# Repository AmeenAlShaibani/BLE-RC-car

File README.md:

The goal of this project is to create an Android app accompanied by a motherboard for an RC car. The motherboard will handle signal, and power distribution to the motors,
and will use BLE technology to connect to the Android app such that the RC car can be controlled remotely.

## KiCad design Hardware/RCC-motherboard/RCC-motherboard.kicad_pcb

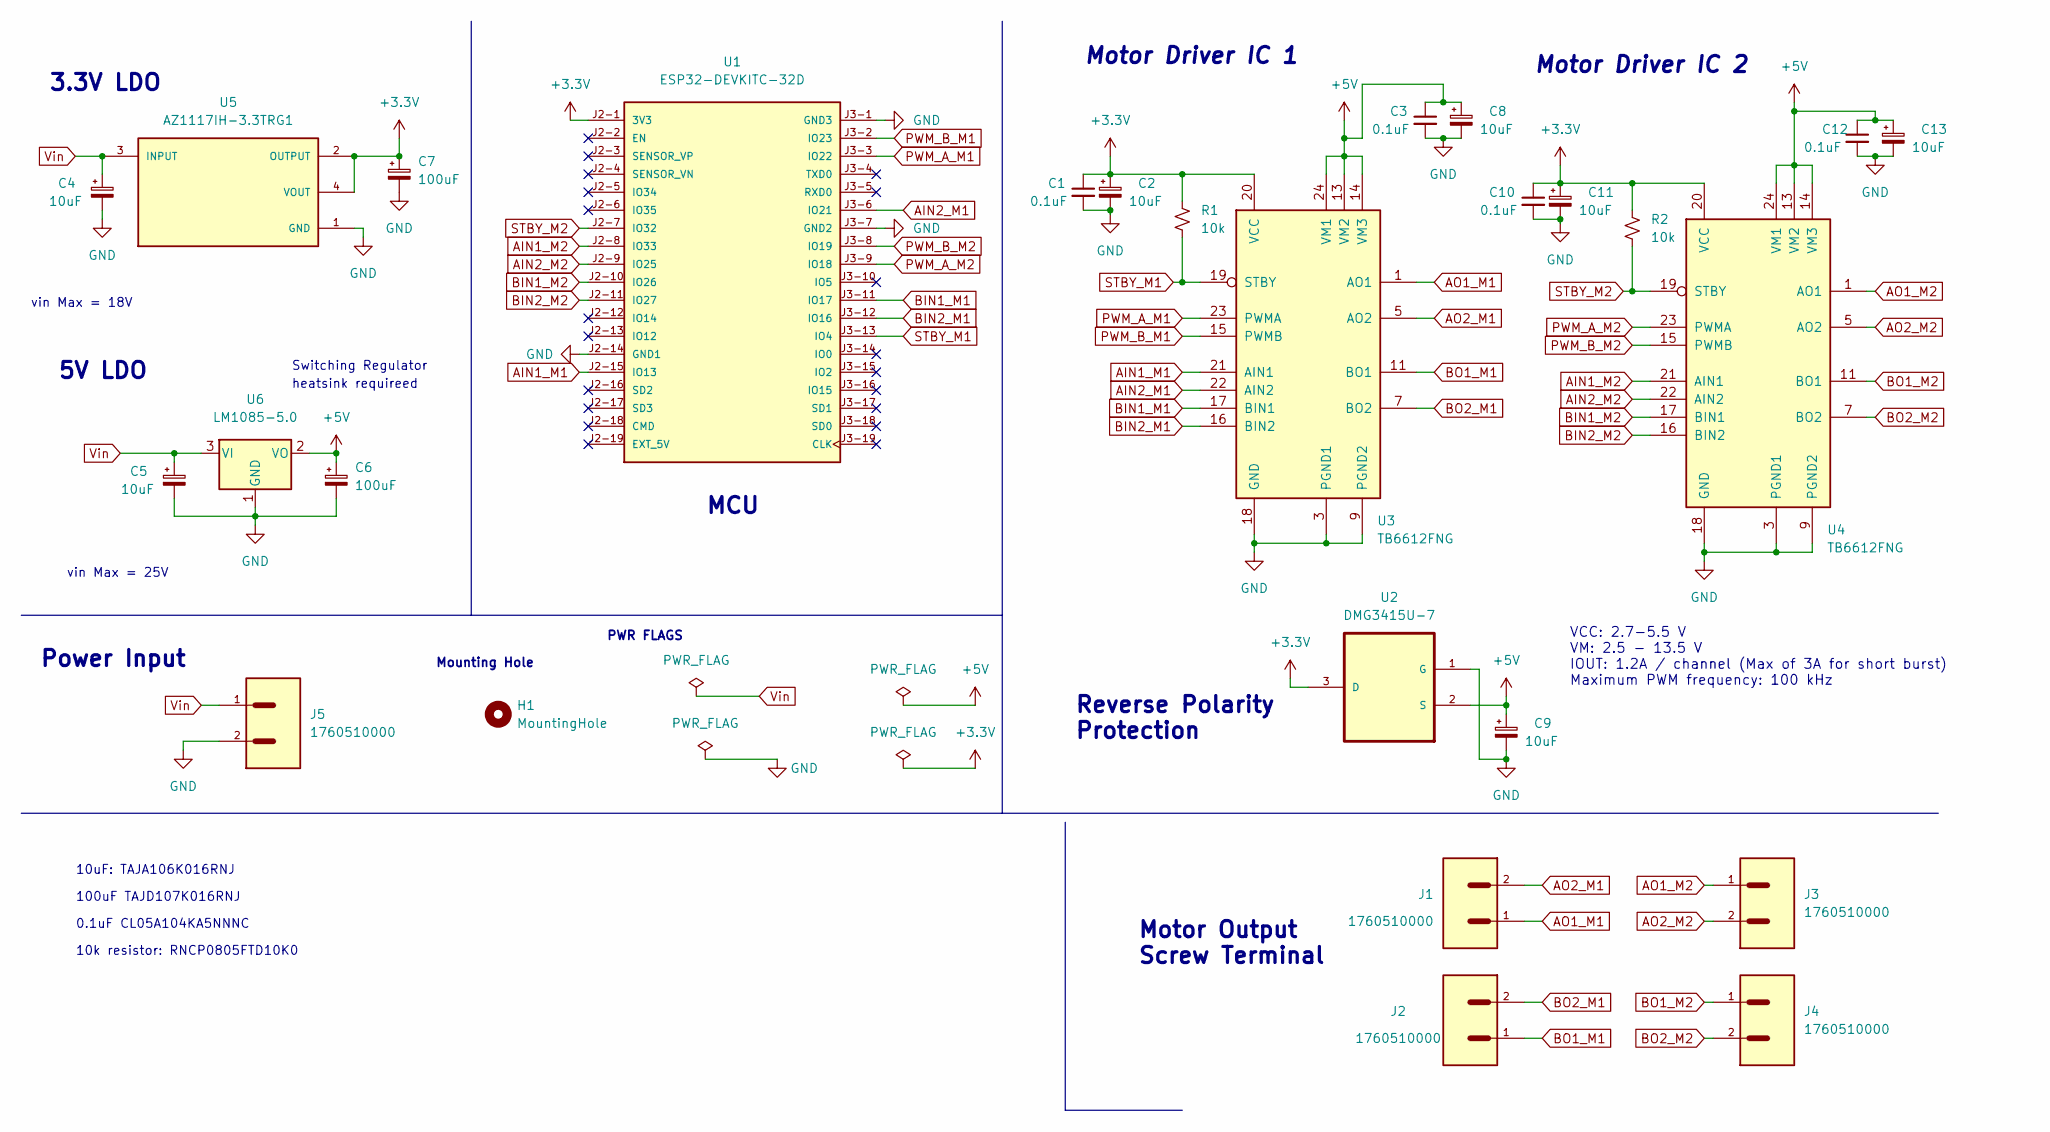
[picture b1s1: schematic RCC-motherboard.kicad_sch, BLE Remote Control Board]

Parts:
C1, C3, C10, C12: 0.1uF; C_0402_1005Metric
C2, C4, C5, C8, C9, C11, C13: 10uF; C_1206_3216Metric
C6, C7: 100uF; CAPMP7343X310N
H1: MountingHole; MountingHole_3.2mm_M3_ISO7380
J1, J2, J3, J4, J5: 1760510000; 1760490000
R1, R2: 10k; R_0805_2012Metric
U1: ESP32-DEVKITC-32D; MODULE_ESP32-DEVKITC-32D; PARTREV V4
U2: DMG3415U-7; SOT95P240X105-3N; MPN DMG3415U-7
U3, U4: TB6612FNG; SSOP-24_5.3x8.2mm_P0.65mm
U5: AZ1117IH-3.3TRG1; SOT230P700X185-4N; PARTREV 2-2
U6: LM1085-5.0; TO-263-3_TabPin2

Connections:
+3V3: C1.1, C2.1, C7.1, C10.1, C11.1, R1.1, R2.1, U1.J2-1 (3V3), U2.3 (D), U3.20 (VCC), U4.20 (VCC), U5.2 (OUTPUT), U5.4 (VOUT)
AIN1_M1: U1.J2-15 (IO13), U3.21 (AIN1)
AIN1_M2: U1.J2-8 (IO33), U4.21 (AIN1)
AIN2_M1: U1.J3-6 (IO21), U3.22 (AIN2)
AIN2_M2: U1.J2-9 (IO25), U4.22 (AIN2)
AO1_M1: J1.1, U3.1 (AO1), U3.2 (AO1)
AO1_M2: J3.1, U4.1 (AO1), U4.2 (AO1)
AO2_M1: J1.2, U3.5 (AO2), U3.6 (AO2)
AO2_M2: J3.2, U4.5 (AO2), U4.6 (AO2)
BIN1_M1: U1.J3-11 (IO17), U3.17 (BIN1)
BIN1_M2: U1.J2-10 (IO26), U4.17 (BIN1)
BIN2_M1: U1.J3-12 (IO16), U3.16 (BIN2)
BIN2_M2: U1.J2-11 (IO27), U4.16 (BIN2)
BO1_M1: J2.1, U3.11 (BO1), U3.12 (BO1)
BO1_M2: J4.1, U4.11 (BO1), U4.12 (BO1)
BO2_M1: J2.2, U3.7 (BO2), U3.8 (BO2)
BO2_M2: J4.2, U4.7 (BO2), U4.8 (BO2)
GND: C1.2, C2.2, C3.2, C4.2, C5.2, C6.2, C7.2, C8.2, C9.2, C10.2, C11.2, C12.2, C13.2, J5.2, U1.J2-14 (GND1), U1.J3-1 (GND3), U1.J3-7 (GND2), U2.1 (G), U3.3 (PGND1), U3.4 (PGND1), U3.9 (PGND2), U3.10 (PGND2), U3.18 (GND), U4.3 (PGND1), U4.4 (PGND1), U4.9 (PGND2), U4.10 (PGND2), U4.18 (GND), U5.1 (GND), U6.1 (GND)
PWM_A_M1: U1.J3-3 (IO22), U3.23 (PWMA)
PWM_A_M2: U1.J3-9 (IO18), U4.23 (PWMA)
PWM_B_M1: U1.J3-2 (IO23), U3.15 (PWMB)
PWM_B_M2: U1.J3-8 (IO19), U4.15 (PWMB)
STBY_M1: R1.2, U1.J3-13 (IO4), U3.19 (STBY)
STBY_M2: R2.2, U1.J2-7 (IO32), U4.19 (STBY)
Vin: C4.1, C5.1, J5.1, U5.3 (INPUT), U6.3 (VI)

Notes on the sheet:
3.3V LDO
Mounting Hole
0.1uF CL05A104KA5NNNC
Motor Driver IC 1
Reverse Polarity Protection
heatsink requireed
PWR FLAGS
VCC: 2.7-5.5 V VM: 2.5 - 13.5 V IOUT: 1.2A / channel (Max of 3A for short burst) Maximum PWM frequency: 100 kHz
MCU
Motor Output Screw Terminal
5V LDO
100uF TAJD107K016RNJ
Power Input
Motor Driver IC 2
10uF: TAJA106K016RNJ
Switching Regulator
vin Max = 18V
10k resistor: RNCP0805FTD10K0
vin Max = 25V

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
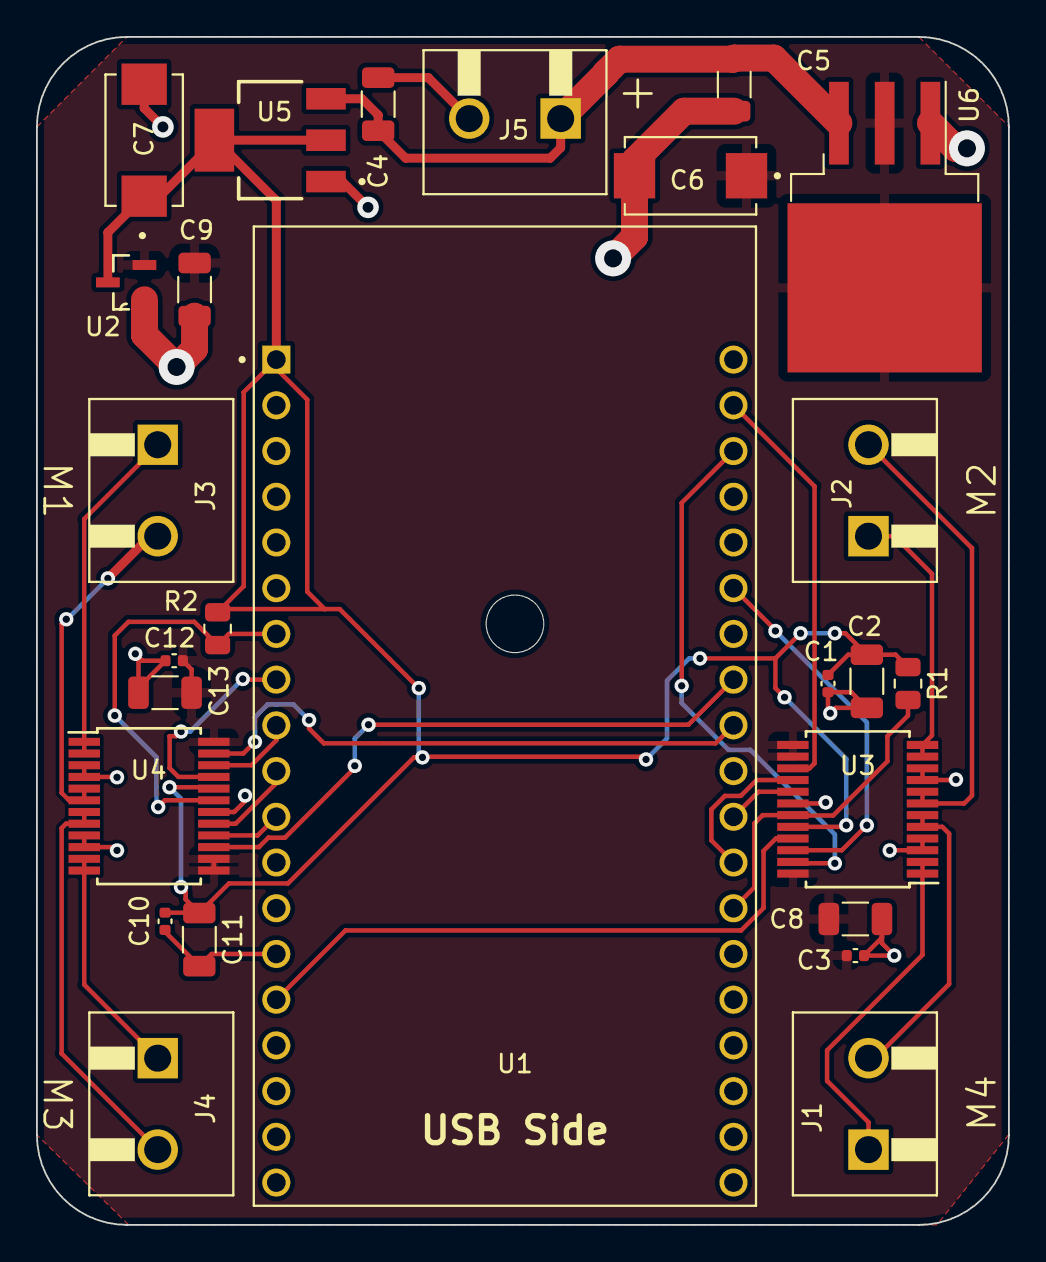
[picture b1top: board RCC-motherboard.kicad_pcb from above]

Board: 2 copper layers, 54.0 x 66.0 mm, 27 parts (0 on the bottom side), 26 nets.

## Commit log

2023-02-28 Added documentation
2023-03-26 Added Motor driver IC
2023-04-03 Added voltage regulators to kicad schematic
2023-04-05 Designed rough layout for board
2023-04-09 Finished PCB Layout
2023-04-12 Produced Gerber and Production files
2023-04-13 Size standarized to mm, and board is ordered
2023-04-19 Created inital Paper Draft
2023-04-27 Board uses ESP32-DEVKITC not narrow version
2023-07-23 Added firmware, and research paper
